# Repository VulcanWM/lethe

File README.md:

# Lethe

Lethe is an educational device aimed at reducing student's screen times by using a speaker to ask questions / convey informations, and using tilts to get user input.

## How it works
- load flashcard sets or MCQ sets onto the ESP32's USB-C connector (it must be in the JSON format expected by Lethe)
- select the flashcard set or MCQ set on the device by tilting through the list of all sets
- if in MCQ mode, a question will be spoken and each different direction responds an option, so to answer you tilt the device in a direction.
- the round will keep on going until all of the questions have been answered correctly
- if in flashcard mode, each flashcard's front side will be spoken out loud
- you can tilt up and down to flip the card and read the other side
- then you tilt left/right to signal whether you want it to be repeated or not

## Inspiration and component reasoning

I made it because high screen time is a problem I face myself, and this device means I can move around while studying. I also wanted to experiment and see if listening rather than reading helps to remember stuff more or not.

Some of the components I'm using and why:
- Seeed Studio XIAO ESP32-S3 Plus rather than not Plus because it has higher Flash and I'm using that to store all the flashcard sets.
- OLED display rather than a colour one because the screen will not be in use during the actual modes because I want the user to focus on sound rather than screens.
- An IMU (BMI270) so that I can accurately detect motions like tilting and flicking in all directions. This means I can use gestures instead of button clicking for user input.
- 1000 mAh LiPo Battery so that there is a reasonable battery life (5 hours) but it doesn't take too long to charge (10 hours).
- JST-PH 2-pin connector so that I can change the battery without needing to remove the solder.

## Hardware
This repository contains all the hardware files you would need to replicate this project. The PCB + schematics was done in the KiCad, and the enclosure was designed in Fusion 360.

The [`pcb-files`](pcb-files) folder contains the KiCad source files (`.kicad_sch`, `.kicad_pro`, `.kicad_pcb`) and the `gerbers.zip` which was used to manufacture the PCB.

The [`cad-files`](cad-files) folder contains `.step`, `.stl` and .`f3d` files for both the top and bottom cases of the enclosure for lethe.
## Firmware
There are 2 main components of the firmware: the code that will be uploaded onto the ESP32, and the code that will be used to transmit json sets on the user's device to the ESP32 when connected to the user's device via USB-C.

Both are located in the [`firmware-files`](firmware-files) folder: `lethe.ino` refers to the ESP32 code, and `upload.py` refers to the file transmission code.

## Assembly

The PCB is mounted to the bottom enclosure using three M2 self-tapping screws through the 2.2 mm mounting holes on the PCB and into standoffs printed as part of the enclosure. Then, the top and bottom parts of the enclosure are fitted together.

## Images
This is what the schematic looks like:

This is what the PCB looks like:

This is what the enclosure (top and bottom case) looks like:

## BOM
Also in the [BOM.csv](BOM.csv) file.

| Name                            | Quantity | Link To Buy                                                                                                                                             | Cost (USD)               |
|---------------------------------|:--------:|---------------------------------------------------------------------------------------------------------------------------------------------------------|--------------------------|
| Seeed Studio XIAO ESP32-S3 Plus |    1     | [Seeed Studio](https://www.seeedstudio.com/Seeed-Studio-XIAO-ESP32S3-Plus-p-6361.html?srsltid=AfmBOooQTaGGdCkQ02MIjwHmLjggawnlMzKeWbwjh-_6AZfB2T0bQeFj) | $7.90 (+$3.80 shipping)  |
| Bosch BMI270                    |    1     | [LCSC](https://www.lcsc.com/product-detail/C2836813.html?s_z=n_q_x_BMI270)                                                                              | $3.64                    |
| MAX98357A                       |    1     | [LCSC](https://www.lcsc.com/product-detail/C910544.html)                                                                                                | $1.34                    |
| 1.3" SH1106 OLED                |    1     | [AliExpress](https://www.aliexpress.com/item/1005006099414855.html)                                                                                     | $4.17 (shipping unknown) |
| JST-PH 2-pin Connector          |    1     | [LCSC](https://www.lcsc.com/product-detail/C131337.html)                                                                                                | $0.71 for 20             |
| 20 mm 8Ω Speaker                |    1     | [LCSC](https://www.lcsc.com/product-detail/C28642279.html)                                                                                              | $0.85                    |
| Button                          |    2     | [LCSC](https://www.lcsc.com/product-detail/C393938.html)                                                                                                | $0.97 for 50             |
| 620 kΩ Resistor                 |    1     | [LCSC](https://www.lcsc.com/product-detail/C2096268.html)                                                                                               | $0.01                    |
| 100 nF Ceramic Capacitor        |    3     | [LCSC](https://www.lcsc.com/product-detail/C92490.html)                                                                                                 | $1.81 for 50             |
| 10 µF Ceramic Capacitor         |    1     | [LCSC](https://www.lcsc.com/product-detail/C17024.html)                                                                                                 | $1.95 for 20             |
| 1000 mAh LiPo Battery           |    1     | [AliExpress](https://www.aliexpress.com/item/1005009294502730.html)                                                                                     | $6.87                    |
| **Total** | | | **$34.02 (excluding unknown AliExpress shipping)** |

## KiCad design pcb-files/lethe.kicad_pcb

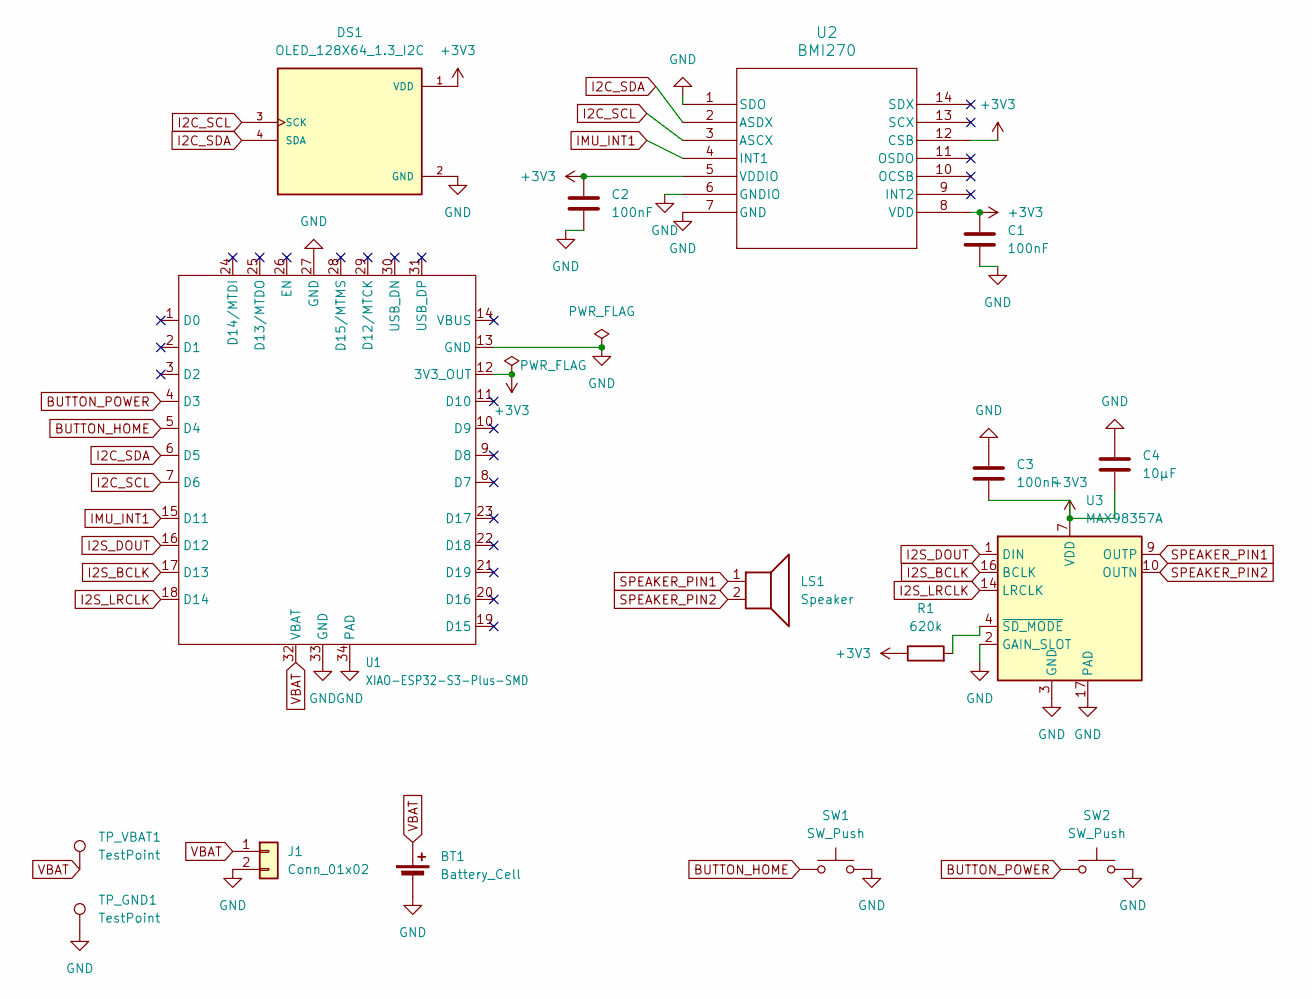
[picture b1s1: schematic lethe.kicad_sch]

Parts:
BT1: Battery_Cell
C1, C2, C3: 100nF; C_0603_1608Metric_Pad1.08x0.95mm_HandSolder
C4: 10µF; C_0805_2012Metric_Pad1.18x1.45mm_HandSolder
DS1: OLED_128X64_1.3_I2C; LCD_OLED_128X64_1.3_I2C; PARTREV NA
J1: Conn_01x02; JST_PH_B2B-PH-K_1x02_P2.00mm_Vertical
LS1: Speaker; Speaker_HDK2008AA_1P2_20mm
R1: 620k; R_0603_1608Metric_Pad0.98x0.95mm_HandSolder
SW1, SW2: SW_Push; SW_PUSH_6mm_H5mm
TP_GND1: TestPoint; TestPoint_THTPad_D1.5mm_Drill0.7mm
TP_VBAT1: TestPoint; TestPoint_THTPad_D1.5mm_Drill0.7mm
U1: XIAO-ESP32-S3-Plus-SMD
U2: BMI270; BMI270_BOS
U3: MAX98357A; TQFN-16-1EP_3x3mm_P0.5mm_EP1.23x1.23mm

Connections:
+3V3: C1.1, C2.1, C3.2, C4.2, DS1.1 (VDD), R1.1, U1.12 (3V3_OUT), U2.5 (VDDIO), U2.8 (VDD), U2.12 (CSB), U3.7 (VDD), U3.8 (VDD)
BUTTON_HOME: SW1.1, U1.5 (D4)
BUTTON_POWER: SW2.1, U1.4 (D3)
GND: BT1.2 (-), C1.2, C2.2, C3.1, C4.1, DS1.2 (GND), J1.2, SW1.2, SW2.2, TP_GND1.1 (1_1), U1.13 (GND), U1.27 (GND), U1.33 (GND), U1.34 (PAD), U2.1 (SDO), U2.6 (GNDIO), U2.7 (GND), U3.2 (GAIN_SLOT), U3.3 (GND), U3.11 (GND), U3.15 (GND), U3.17 (PAD)
I2C_SCL: DS1.3 (SCK), U1.7 (D6), U2.3 (ASCX)
I2C_SDA: DS1.4 (SDA), U1.6 (D5), U2.2 (ASDX)
I2S_BCLK: U1.17 (D13), U3.16 (BCLK)
I2S_DOUT: U1.16 (D12), U3.1 (DIN)
I2S_LRCLK: U1.18 (D14), U3.14 (LRCLK)
IMU_INT1: U1.15 (D11), U2.4 (INT1)
unnamed: R1.2, U3.4 (~SD_MODE)
SPEAKER_PIN1: LS1.1, U3.9 (OUTP)
SPEAKER_PIN2: LS1.2, U3.10 (OUTN)
VBAT: BT1.1 (+), J1.1, TP_VBAT1.1 (1_1), U1.32 (VBAT)

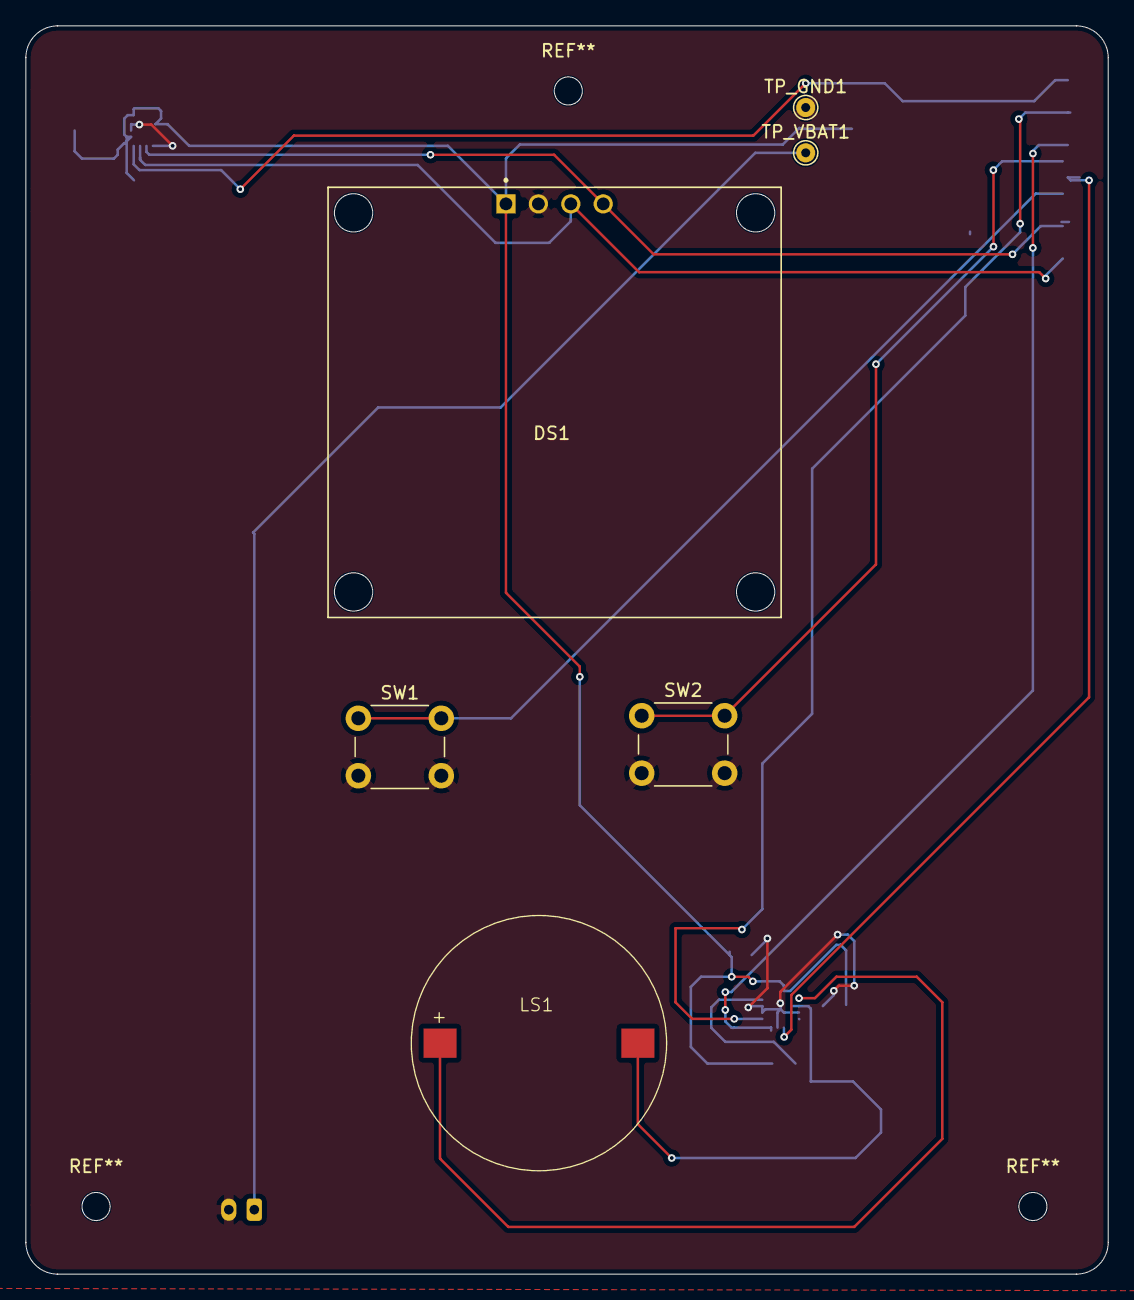
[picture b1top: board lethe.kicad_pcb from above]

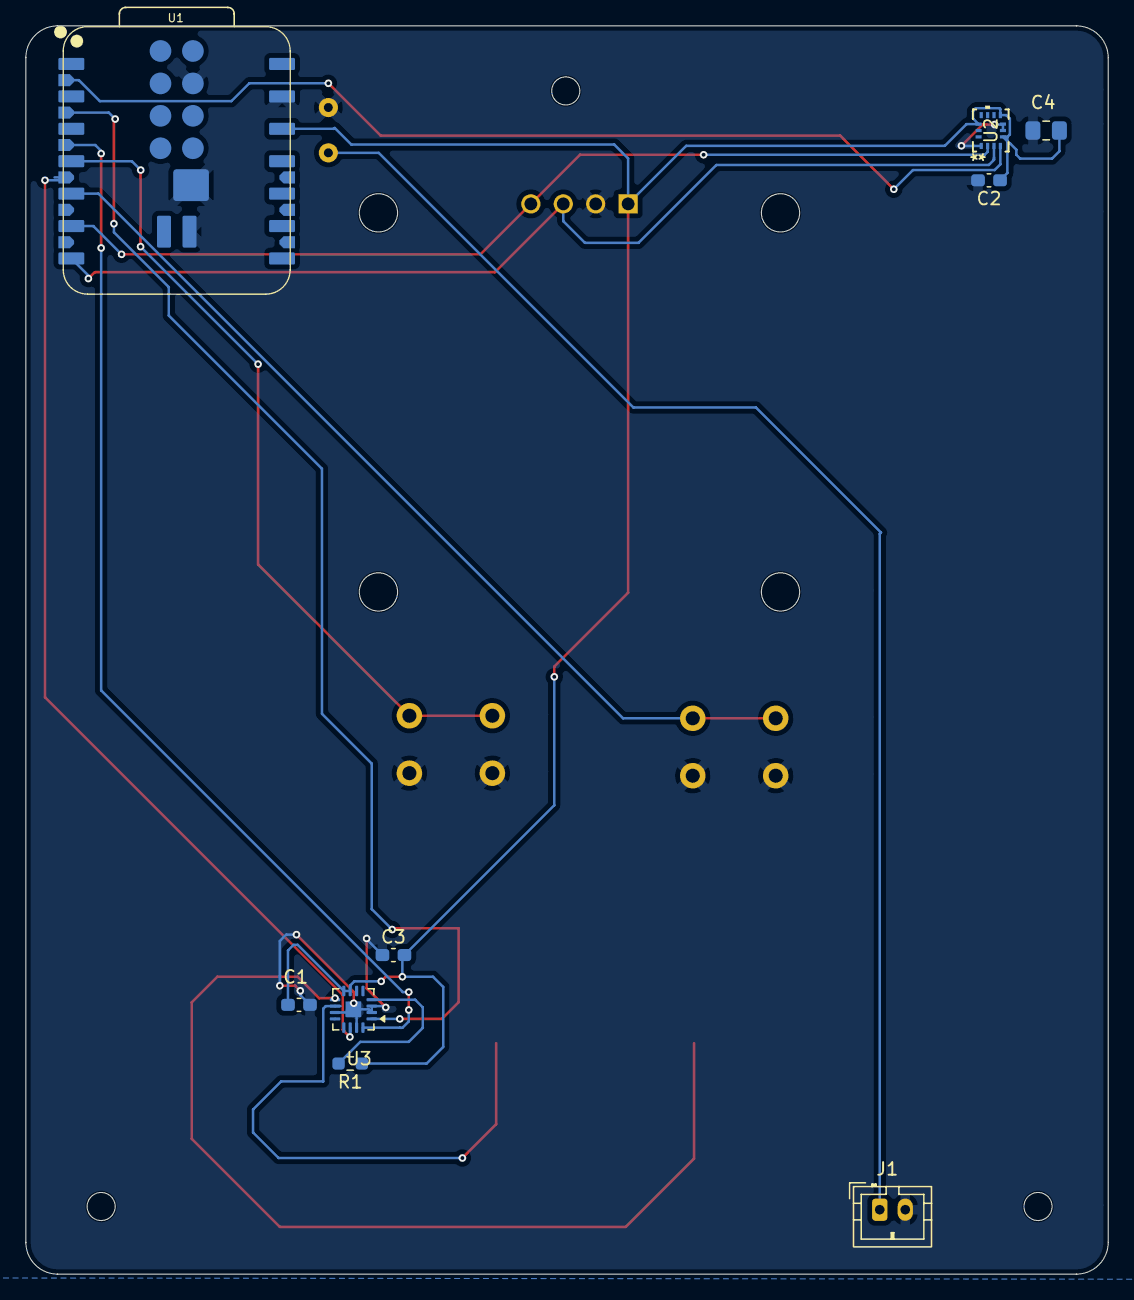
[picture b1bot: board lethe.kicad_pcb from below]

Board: 2 copper layers, 84.8 x 97.8 mm, 15 parts (9 on the bottom side), 14 nets.

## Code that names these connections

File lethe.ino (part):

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#include <vector>

// buttons
#define BUTTON_POWER D3
#define BUTTON_HOME D4

// i2c (for oled and imu)
#define SDA_PIN D5
#define SCL_PIN D6

// imu interrupt
#define IMU_INT1 D11

// i2s (for amplifier)
#define I2S_DOUT D12
#define I2S_BCLK D13
#define I2S_LRCLK D14

// for LittleFS
#define FORMAT_LITTLEFS_IF_FAILED true
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  delay(100);

  esp_sleep_enable_ext0_wakeup(
    (gpio_num_t)BUTTON_POWER,
    0
  );

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
  display.begin();

  pinMode(BUTTON_POWER, INPUT_PULLUP);
  pinMode(BUTTON_HOME, INPUT_PULLUP);

  speech.setVoice(voice_en);

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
